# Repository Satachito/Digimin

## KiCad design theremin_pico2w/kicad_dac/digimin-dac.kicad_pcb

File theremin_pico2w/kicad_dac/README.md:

# Digimin DAC 基板

Digimin DAC 版の親基板。Pico 2 WH をピンソケットに挿し、PCM5102A モジュールを直接はんだ付けし、センサーはピンヘッダーからメスメスのケーブルでつなぐ。ケースは使わず、秋月のアクリル板 LPMxxxT2-B（77 × 100mm、縦に使う）をスペーサーで上に付ける。DAC モジュールは上の縁に横置きし、3.5mm ジャックの口（モジュールの長い辺に向いている）を上に向ける。その下に Pico（USB は上向き）。Pico はピンソケットで約 8.5mm 浮くので、USB のプラグは DAC モジュールの右半分（6 ピン側）の上を通り、左の端のジャックとは当たらない。

## 仕様

- 2 層、77 × 100mm（縦）、角 R3、厚さ 1.6mm。外形と取り付け穴はアクリル板に合わせる（φ3.2 の穴 4 つ、間隔 66 × 89mm、各辺から 5.5mm）
- 部品はすべてスルーホール。JLCPCB には基板だけを頼めばよい（実装サービスは不要）
- 両面ベタ GND。Pico のアンテナ（USB の反対の端）の下には銅箔を置かない
- 製造データ: [fabrication/digimin-dac-gerber.zip](fabrication/digimin-dac-gerber.zip)（ガーバーとドリル。JLCPCB にそのままアップロードできる）
- 基板のデータは [make_board.py](make_board.py) で作っている（KiCad 10 付属の Python で実行）。回路図はなく、つながりは下の表のとおり

## 部品

| 記号 | 部品 | 数 |
|---|---|---|
| U1 | Raspberry Pi Pico 2 WH ＋ 1×20 ピンソケット（2.54mm） | 1（ソケット 2） |
| J4 | PCM5102A モジュール（紫、17 × 32mm）。付属の 6 ピンのピンヘッダーで直接はんだ付け | 1 |
| P1 | DAC の枕（3.5mm ジャックの下。モジュールの左の端のすぐ内側に縦に 2 つ、φ1.0、間隔 9mm。どこにもつながっていない） | — |
| C1 | 電解コンデンサ 100µF 10V 以上（φ6.3、ピッチ 2.5mm） | 1 |
| C2 | セラミックコンデンサ 0.1µF（ピッチ 2.5mm） | 1 |
| J1 | 1×3 ピンヘッダー ＋ ジャンパーキャップ（Wi-Fi） | 1 |
| J2, J3 | 1×6 ピンヘッダー（音程センサー、音量センサー） | 2 |
| H1–H4 | M3 のスペーサーとねじ（アクリル板用） | 4 組 |

## つながり

| Pico | つなぐ先 |
|---|---|
| GP0（1） | DAC LCK |
| GP1（2） | DAC BCK |
| GP2（4） | DAC DIN |
| GP5（7） | J1 の GP5 |
| GP9（12） | J1 の GP9 |
| GP11 / GP12 / GP13（15 / 16 / 17） | J2（音程）の XSHUT / SDA / SCL |
| GP18 / GP19 / GP20（24 / 25 / 26） | J3（音量）の SDA / SCL / XSHUT |
| 3V3（36） | J2、J3 の VIN |
| VBUS（40） | DAC VIN、C1、C2 |
| GND | DAC GND と SCK、J1 の中央、J2、J3 の GND、C1、C2（ベタ GND） |

- J2、J3 の並びはセンサーと同じで、上から XSHUT / GPIO1（未接続）/ SDA / SCL / GND / VIN。
- Wi-Fi のジャンパー（J1）: GP5–GND でオフ、キャップなしでオン、GND–GP9 でパスワードなしでオン。

## 組み立て

1. ピンソケット、ピンヘッダー、C1（向きに注意。長い足が +）、C2 をはんだ付けする。
2. DAC モジュールの裏のジャンパーを先にはんだ付けしておく（H1 / H2 / H4 を L、H3 を H）。
3. DAC モジュールに 6 ピンのピンヘッダーを付け、部品面を上にして J4 に挿し、ジャックの口が基板の上の縁に来るようにしてはんだ付けする（ジャックは左の端、6 ピンは右の端で、上から VIN / GND / LCK / DIN / BCK / SCK）。
4. 枕: P1 の 2 つの穴に針金を U の字に通し、モジュールの裏（ジャックの下）に当たる高さ（ピンヘッダーの樹脂の厚み、約 2.5mm）にしてはんだ付けする。ジャックの足が裏に出ているので、針金は熱収縮チューブなどで絶縁するか、足に触れない高さにする（触れると左右と GND がつながって音がおかしくなる）。
5. Pico 2 WH をソケットに挿す（USB が上、DAC 側）。
6. センサーを針金で固定し、メスメスのケーブルで J2、J3 につなぐ。

## 注意

- アクリル板は音量センサーの真上に来る。アクリル越しでは板の反射を拾って測れないので、センサーの上のアクリルに穴（φ10mm 程度）をあけるか、センサーを板より上に出す。
- USB のプラグは DAC モジュールの上（基板から約 8mm 以上）を通る。DAC の 6 ピンのピンヘッダーは、モジュールの上に出る側を短くしておく（モジュールの上 3mm 程度まで）。

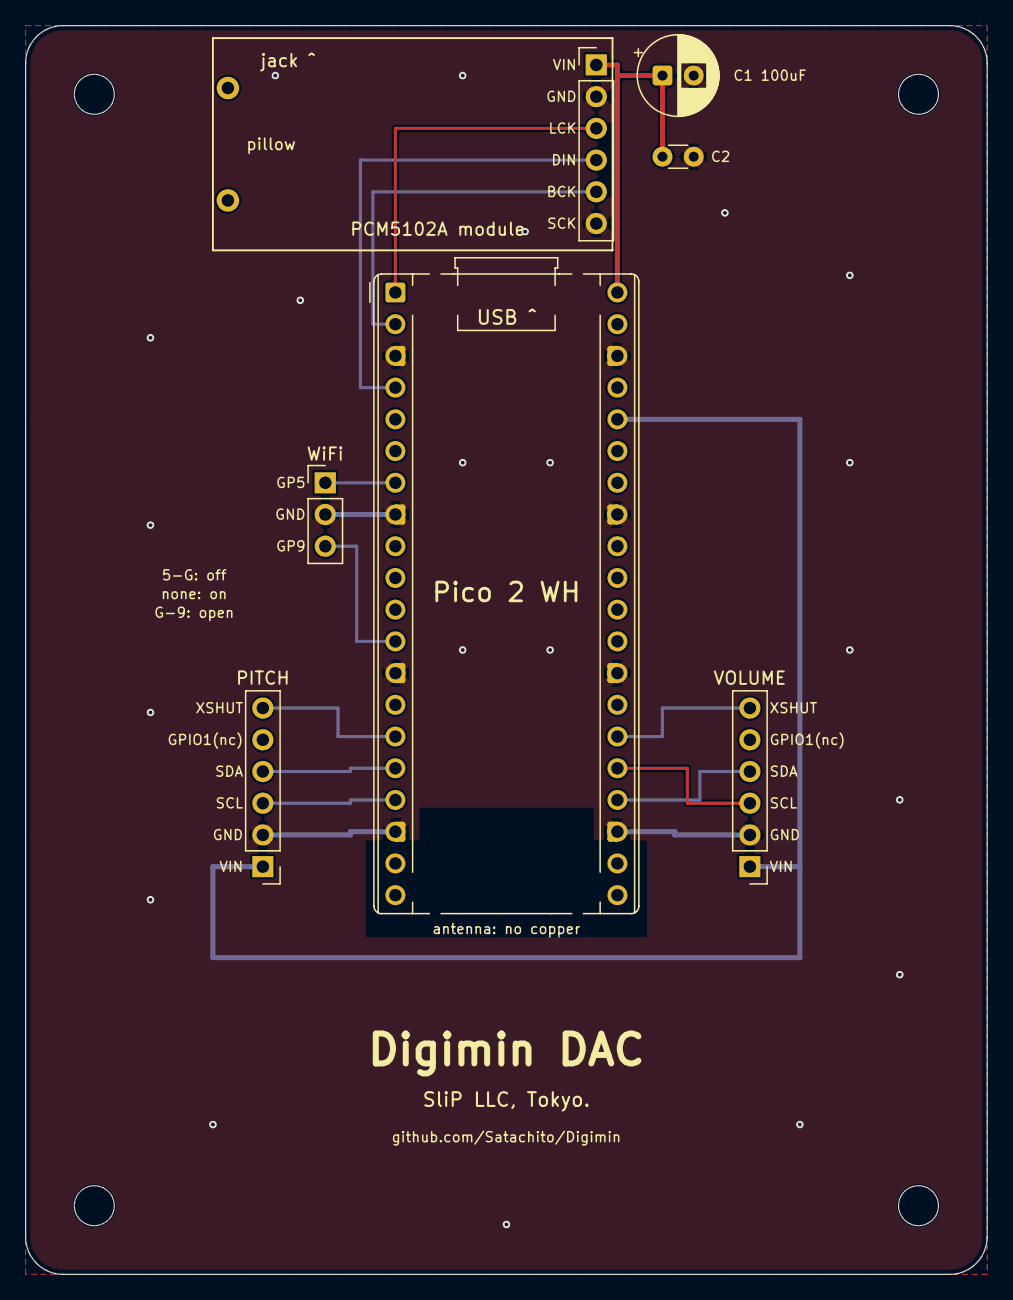
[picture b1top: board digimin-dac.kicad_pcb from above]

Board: 2 copper layers, 77.0 x 100.0 mm, 12 parts (0 on the bottom side), 14 nets.

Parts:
C1: 100uF; CP_Radial_D6.3mm_P2.50mm
C2: 0.1uF; C_Disc_D3.0mm_W1.6mm_P2.50mm
H1, H2, H3, H4: M3; MountingHole_3.2mm_M3
J1: WiFi; PinHeader_1x03_P2.54mm_Vertical
J2: PITCH; PinHeader_1x06_P2.54mm_Vertical
J3: VOLUME; PinHeader_1x06_P2.54mm_Vertical
J4: PCM5102A; PinHeader_1x06_P2.54mm_Vertical
P1: pillow
U1: Pico 2 WH; RaspberryPi_Pico_Common_THT

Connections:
+3V3: J2.1, J3.1, U1.36
BCK: J4.5, U1.2
DIN: J4.4, U1.4
GND: C1.2, C2.2, J1.2, J2.2, J3.2, J4.2, J4.6, U1.3, U1.8, U1.13, U1.18, U1.23, U1.28, U1.33, U1.38
LCK: J4.3, U1.1
P_SCL: J2.3, U1.17
P_SDA: J2.4, U1.16
P_XSHUT: J2.6, U1.15
VBUS: C1.1, C2.1, J4.1, U1.40
V_SCL: J3.3, U1.25
V_SDA: J3.4, U1.24
V_XSHUT: J3.6, U1.26
WIFI_OFF: J1.1, U1.7
WIFI_OPEN: J1.3, U1.12

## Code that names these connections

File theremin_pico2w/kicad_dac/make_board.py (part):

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

# I2S: DAC の 6 ピン列から左へ出て、モジュールの下を通って Pico の左の列の上の端へ
track("LCK", [(DPX, DAC_Y["LCK"]), (PX, DAC_Y["LCK"]), pin(1)], F)
track("BCK", [(DPX, DAC_Y["BCK"]), (PX - 1.8, DAC_Y["BCK"]), (PX - 1.8, pin(2)[1]), pin(2)], B)
track("DIN", [(DPX, DAC_Y["DIN"]), (PX - 2.8, DAC_Y["DIN"]), (PX - 2.8, pin(4)[1]), pin(4)], B)

# VBUS: Pico 40 番 → DAC VIN、C1、C2（表）
track("VBUS", [pin(40), (Rr, DAC_Y["VIN"]), (DPX, DAC_Y["VIN"])], F, 0.4)
track("VBUS", [(Rr, C1Y), (C1X, C1Y), (C2X, C2Y)], F, 0.4)

# Wi-Fi ジャンパー
track("WIFI_OFF", [pin(7), (JX, JY)], B)
track("GND", [pin(8), (JX, JY + 2.54)], B, 0.4)
track("WIFI_OPEN", [pin(12), (PX - 3.1, pin(12)[1]), (PX - 3.1, JY + 5.08), (JX, JY + 5.08)], B)

# 音程センサー（左）
track("P_XSHUT", [pin(15), (PX - 4.6, pin(15)[1]), (PX - 4.6, SY["XSHUT"]), (SLX, SY["XSHUT"])], B)
track("P_SDA", [pin(16), (PX - 3.6, pin(16)[1]), (PX - 3.6, SY["SDA"]), (SLX, SY["SDA"])], B)
track("P_SCL", [pin(17), (PX - 3.6, pin(17)[1]), (PX - 3.6, SY["SCL"]), (SLX, SY["SCL"])], B)
track("GND", [pin(18), (PX - 3.6, pin(18)[1]), (PX - 3.6, SY["GND"]), (SLX, SY["GND"])], B, 0.4)

# 音量センサー（右）
track("V_XSHUT", [pin(26), (Rr + 3.6, pin(26)[1]), (Rr + 3.6, SY["XSHUT"]), (SRX, SY["XSHUT"])], B)
track("V_SCL", [pin(25), (Rr + 5.6, pin(25)[1]), (Rr + 5.6, SY["SCL"]), (SRX, SY["SCL"])], F)
track("V_SDA", [pin(24), (Rr + 6.6, pin(24)[1]), (Rr + 6.6, SY["SDA"]), (SRX, SY["SDA"])], B)
track("GND", [pin(23), (Rr + 4.6, pin(23)[1]), (Rr + 4.6, SY["GND"]), (SRX, SY["GND"])], B, 0.4)

# 3V3: Pico 36 番 → 右のセンサー → 基板の下を回って左のセンサー（Pico のアンテナの下は通らない）
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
